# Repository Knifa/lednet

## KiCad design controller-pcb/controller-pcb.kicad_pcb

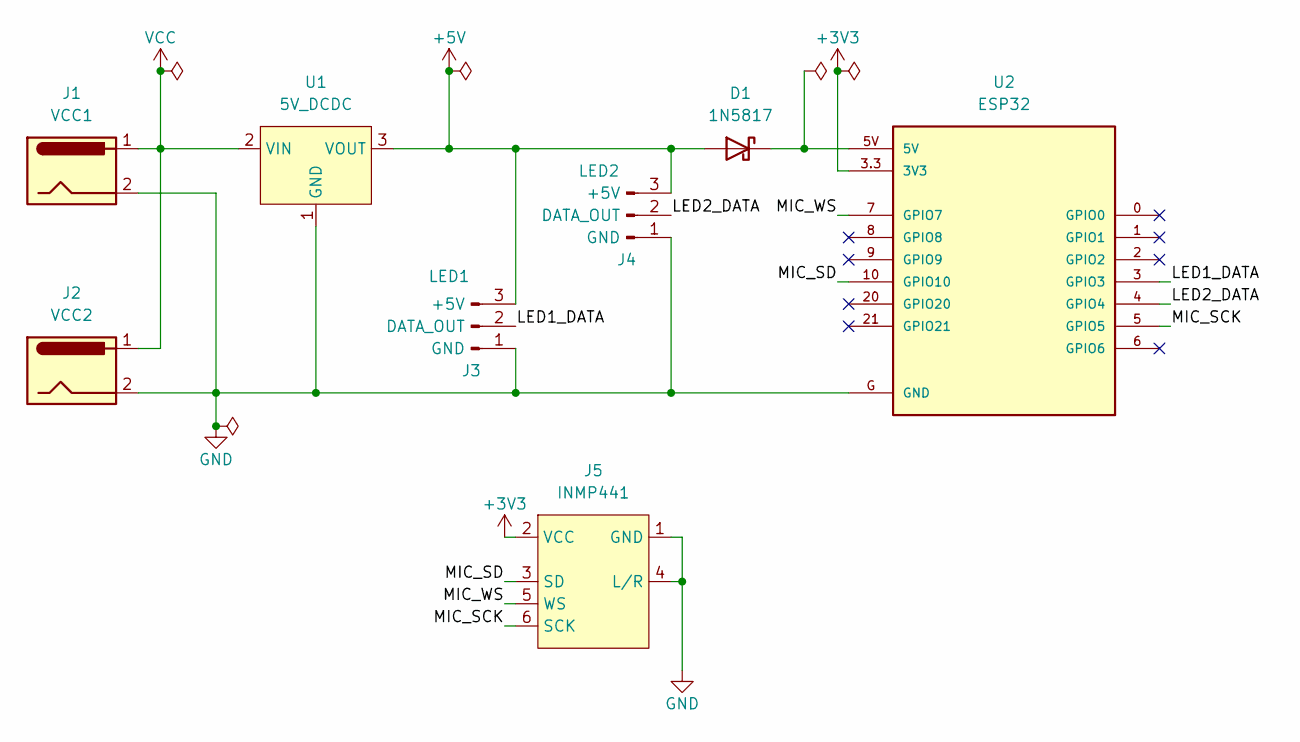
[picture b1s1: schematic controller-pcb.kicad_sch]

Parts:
D1: 1N5817; D_DO-41_SOD81_P10.16mm_Horizontal
J1: VCC1; BarrelJack_Horizontal
J2: VCC2; BarrelJack_Horizontal
J3: LED1; LED_Wire_Connector
J4: LED2; LED_Wire_Connector
J5: INMP441; INMP441_Breakout
U1: 5V_DCDC; Converter_DCDC_8A_Generic
U2: ESP32; MODULE_ESP32-C3_SUPERMINI

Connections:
+3V3: J5.2 (VCC), U2.3.3 (3V3)
+5V: D1.2 (A), J3.3 (+5V), J4.3 (+5V), U1.3 (VOUT)
/LED1_DATA: J3.2 (DATA_OUT), U2.3 (GPIO3)
/LED2_DATA: J4.2 (DATA_OUT), U2.4 (GPIO4)
/MIC_SCK: J5.6 (SCK), U2.5 (GPIO5)
/MIC_SD: J5.3 (SD), U2.10 (GPIO10)
/MIC_WS: J5.5 (WS), U2.7 (GPIO7)
GND: J1.2, J2.2, J3.1 (GND), J4.1 (GND), J5.1 (GND), J5.4 (L/R), U1.1 (GND), U2.G (GND)
unnamed: D1.1 (K), U2.5V
VCC: J1.1, J2.1, U1.2 (VIN)

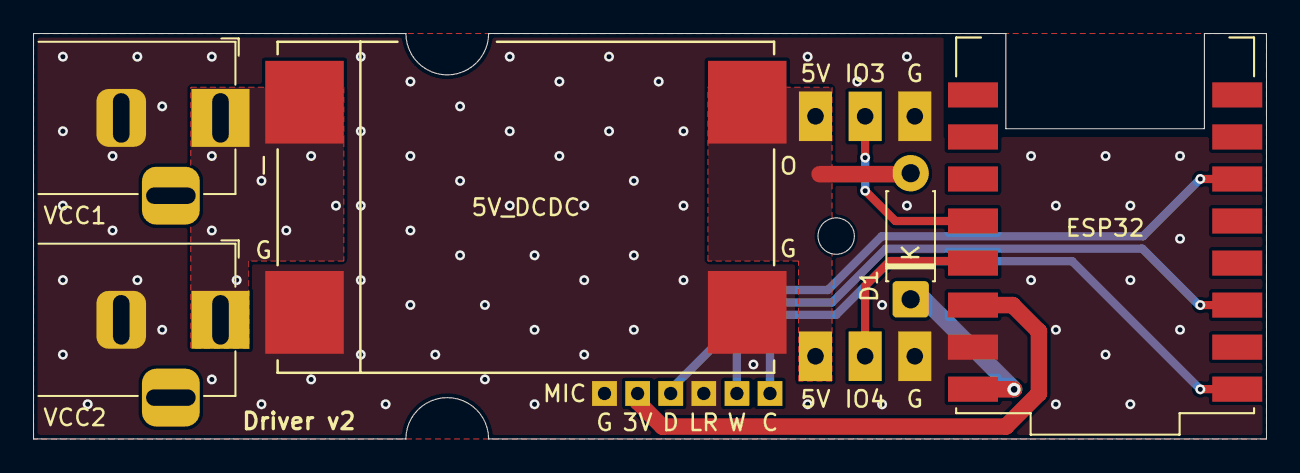
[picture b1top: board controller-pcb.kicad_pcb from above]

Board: 2 copper layers, 74.5 x 24.5 mm, 8 parts (0 on the bottom side), 10 nets.

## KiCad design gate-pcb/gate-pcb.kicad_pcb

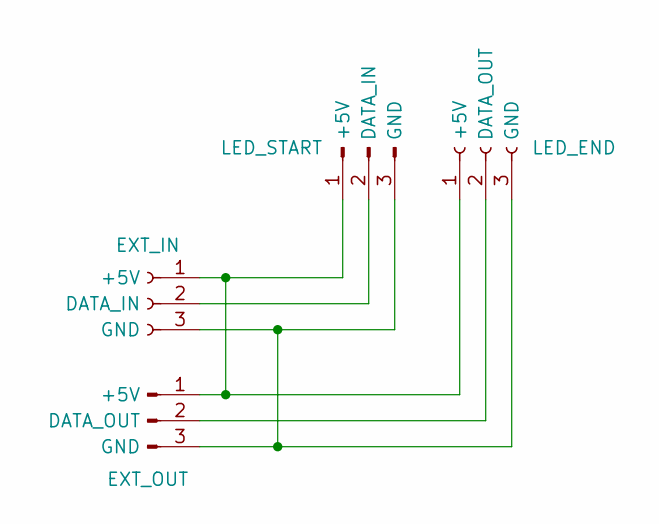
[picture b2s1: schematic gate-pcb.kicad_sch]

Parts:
J1: EXT_IN; LED_Wire_Connector
J2: EXT_OUT; LED_Wire_Connector
J3: LED_START; LED_Wire_Connector
J4: LED_END; LED_Wire_Connector

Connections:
unnamed: J1.1 (+5V), J2.1 (+5V), J3.1 (+5V), J4.1 (+5V)
unnamed: J1.2 (DATA_IN), J3.2 (DATA_IN)
unnamed: J1.3 (GND), J2.3 (GND), J3.3 (GND), J4.3 (GND)
unnamed: J2.2 (DATA_OUT), J4.2 (DATA_OUT)

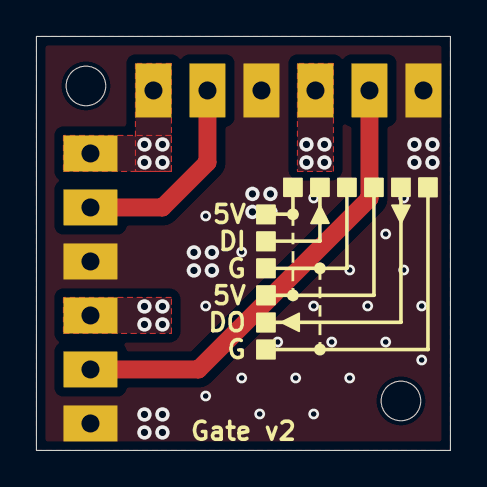
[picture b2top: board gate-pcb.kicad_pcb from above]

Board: 2 copper layers, 23.0 x 23.0 mm, 4 parts (0 on the bottom side), 4 nets.

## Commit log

2026-01-05 fixup gitignore
2026-01-05 fix backside 5v fill to connect with pads
2026-01-05 fix dc jack polarity
